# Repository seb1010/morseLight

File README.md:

# Text to Morse Code

## Project Overview

In this project I made a light blink in morse code. You are able to write to a text file and the corresponding morse code can be programmed into the memory of a microcontroller. PWM was used to when turning on and off light for smooth transitions. Input length was restricted by the program memory of the microcontroller. There is also a switch to turn off the morse code and keep the light on all the time.

## Implementation

### Microcontroller
**Name:** ATTiny13
**Memory:** 1k of program memory

### Programming Languages Used
* C
    * Converting text to a binary code (morse code), expressed as hex in a ascii file.
    * `textToMorse.c`
    * This output file can be read directly by the assembler I used (avra)
    * The assembler writes the binary code into the program memory

* Assembly (for ATTiny13)
    * loads one byte at a time from the program memory
    * then sends one bit at a time to a pin using PWM to soften transitions
    * `morseOut.asm`
    * Pulse with Modulation(PWM): microcontroller has built in PWM
        * Accidentally chose pins with no built in PWM
        * To remedy this, implemented PWM in software

### Dimming
* I wanted to be able to control the maximum brightness of the light so it could be used durring the day or at night.
* With only 8 bits of PWM on the microcontroller this would be impossible to achieve while keeping the transitions looking smooth even at low brightnesses. 
* This is why I included the potentiometer and transitor
* It isn't a perfect circuit as it is tempurature sensitive and sensitive to changes in supply voltage, but I wasn't able to notice these issues when using the light.

### PCB
I etched the PCB at home. Mixed through-hole and surface mount parts. 

#### Components
* 1 transistor
* 5 LED's
* 1 potentiometer

## Project Result and Takeaways

### Results
* It worked ok. Storing morse code the way I did was not space efficient for long messages. Also the c program was very sensitive to white space, so you have to be carful with formatting. That could definitly use improvement.

* [Video of Light Blinking on YouTube](https://youtu.be/B2VOs5uNV_o)

### Takeaways
I wish I had included reverse polarity protection.
I created the pcb before finishing the code. However, there was no need for this. I could have got the circuit woringing on a breadboard before making the PCB and this would have prevented the mistake of using the wrong pin to control the leds. Alternativily I could have been more careful and not assumed all pins had PWM capability.

If I were to do this project again I would modify the pcb instead of software to deal with PWM error. I knew I was only making one so it seemed like a more eligant solution to keep the pcb intact, but now I dont think that was the best option. 
Its nice to have different programs to integrate.

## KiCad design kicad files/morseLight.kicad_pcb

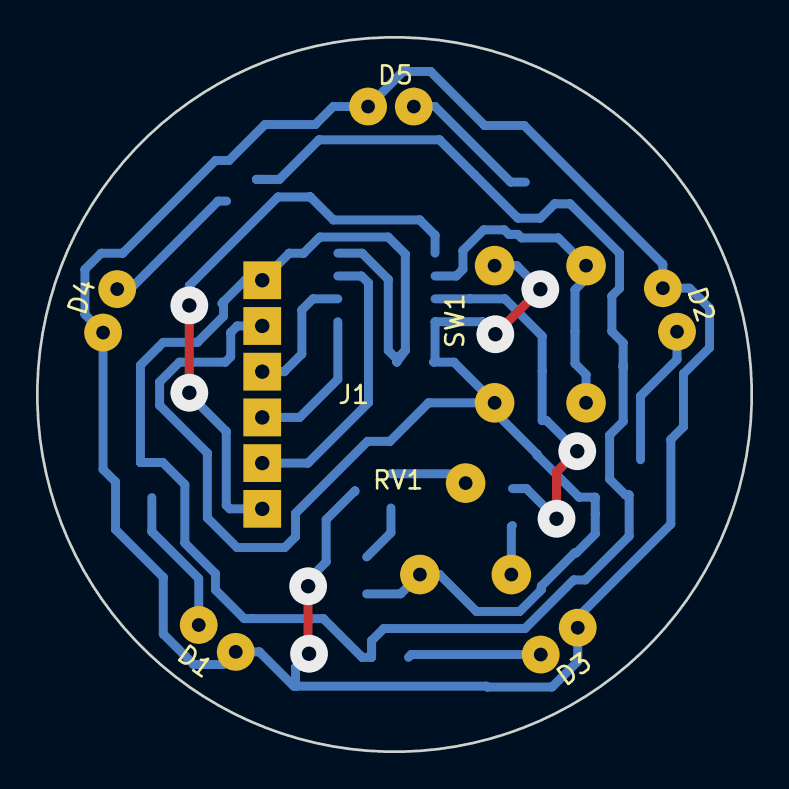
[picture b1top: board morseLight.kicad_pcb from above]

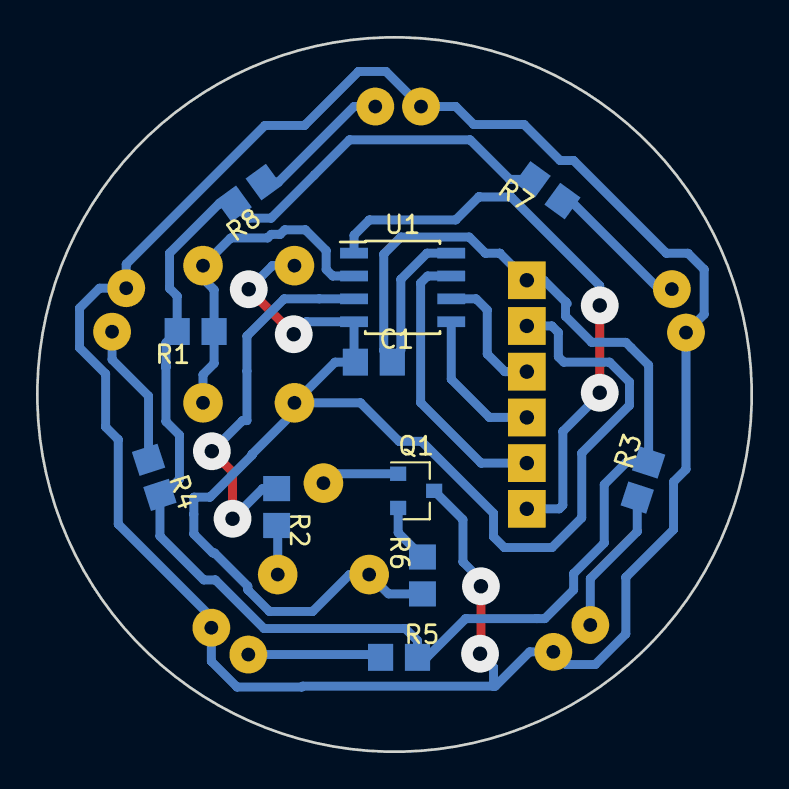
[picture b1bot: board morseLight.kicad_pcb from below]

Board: 2 copper layers, 39.7 x 39.7 mm, 19 parts (11 on the bottom side), 17 nets.

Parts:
C1: C; 0805_2
D1, D2, D3, D4, D5: LED; 5mmLed
J1: Conn_01x06; 6pinConn
Q1: MMBT3904; SOT-23
R1, R2, R3, R4, R5, R6, R7, R8: R; 0805_2
RV1: POT; bluePot
SW1: NOSwitch; SmollSwitch
U1: ATTINY13-20SSU; SOIC-8_3.9x4.9mm_Pitch1.27mm

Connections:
GND: C1.2, J1.2, R6.2, RV1.3, SW1.2, U1.4
unnamed: D1.1, D2.1, D3.1, D4.1, D5.1, Q1.3
unnamed: D1.2, R3.2
unnamed: D2.2, R4.2
unnamed: D3.2, R5.2
unnamed: D4.2, R7.2
unnamed: D5.2, R8.2
unnamed: J1.3, U1.6
unnamed: J1.4, U1.5
unnamed: J1.5, U1.7
unnamed: J1.6, U1.1
unnamed: Q1.1, RV1.2
unnamed: Q1.2, R6.1
unnamed: R1.2, SW1.1, U1.2
unnamed: R2.1, RV1.1
unnamed: R2.2, U1.3
VCC: C1.1, J1.1, R1.1, R3.1, R4.1, R5.1, R7.1, R8.1, U1.8

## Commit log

2021-07-24 Add existing fil
2021-07-24 added morseOut.asm
2021-07-24 trying to add image
2021-07-24 trying to alter image
2021-07-24 formatting
2021-07-24 kicad files
2021-07-24 slight edit
2021-07-24 cleaned up textToMorse.c
2021-07-24 adding video link
